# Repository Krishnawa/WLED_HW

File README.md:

# WLED_HW
a WLED based ESP12F Hardware
You can find more information about WLED here: https://github.com/Aircoookie/WLED

## Hardware photo

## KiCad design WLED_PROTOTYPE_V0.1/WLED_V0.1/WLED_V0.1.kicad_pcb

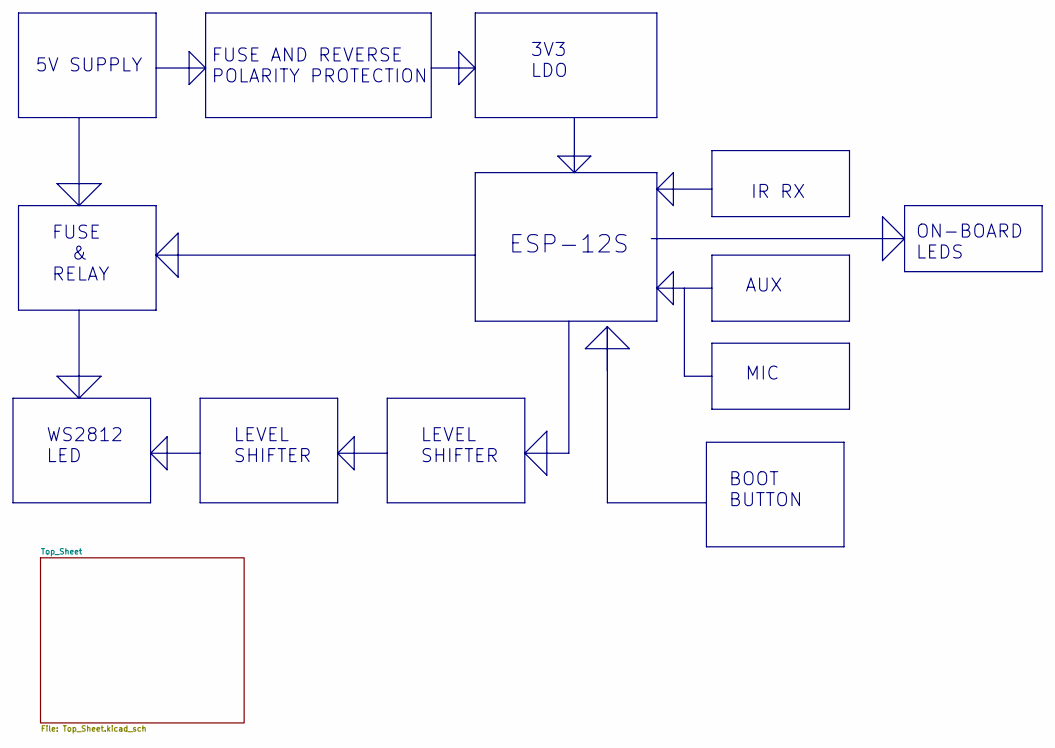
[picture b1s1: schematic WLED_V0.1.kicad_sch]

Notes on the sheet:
FUSE AND REVERSE POLARITY PROTECTION
BOOT BUTTON
WS2812 LED
LEVEL SHIFTER
ESP-12S
3V3 LDO
IR RX
FUSE & RELAY
AUX
MIC
5V SUPPLY
ON-BOARD LEDS

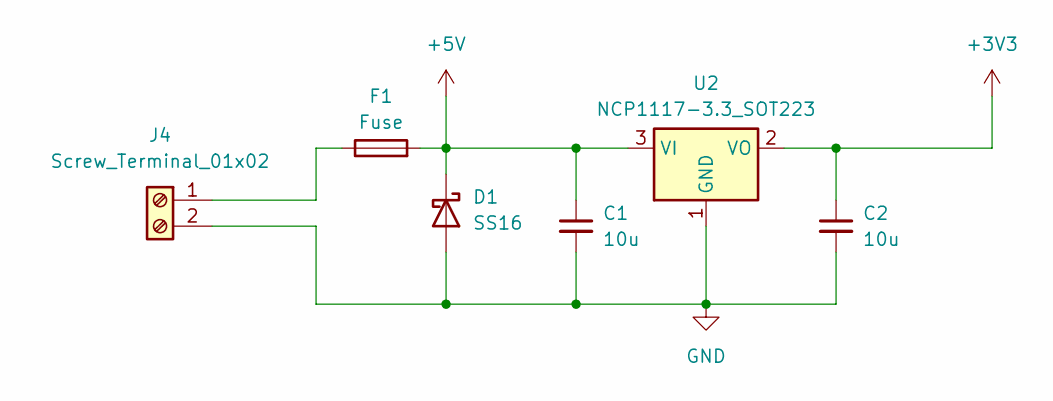
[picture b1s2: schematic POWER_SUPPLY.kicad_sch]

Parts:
C1, C2: 10u; C_0805_2012Metric
D1: SS16; D_SMA
F1: Fuse; Fuse_0805_2012Metric
J4: Screw_Terminal_01x02; TerminalBlock_Phoenix_MKDS-1,5-2_1x02_P5.00mm_Horizontal
U2: NCP1117-3.3_SOT223; SOT-223-3_TabPin2

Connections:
+5V: C1.1, D1.1 (K), F1.2, U2.3 (VI); also elsewhere on the board
GND: C1.2, C2.2, D1.2 (A), J4.2, U2.1 (GND); also elsewhere on the board
unnamed: F1.1, J4.1

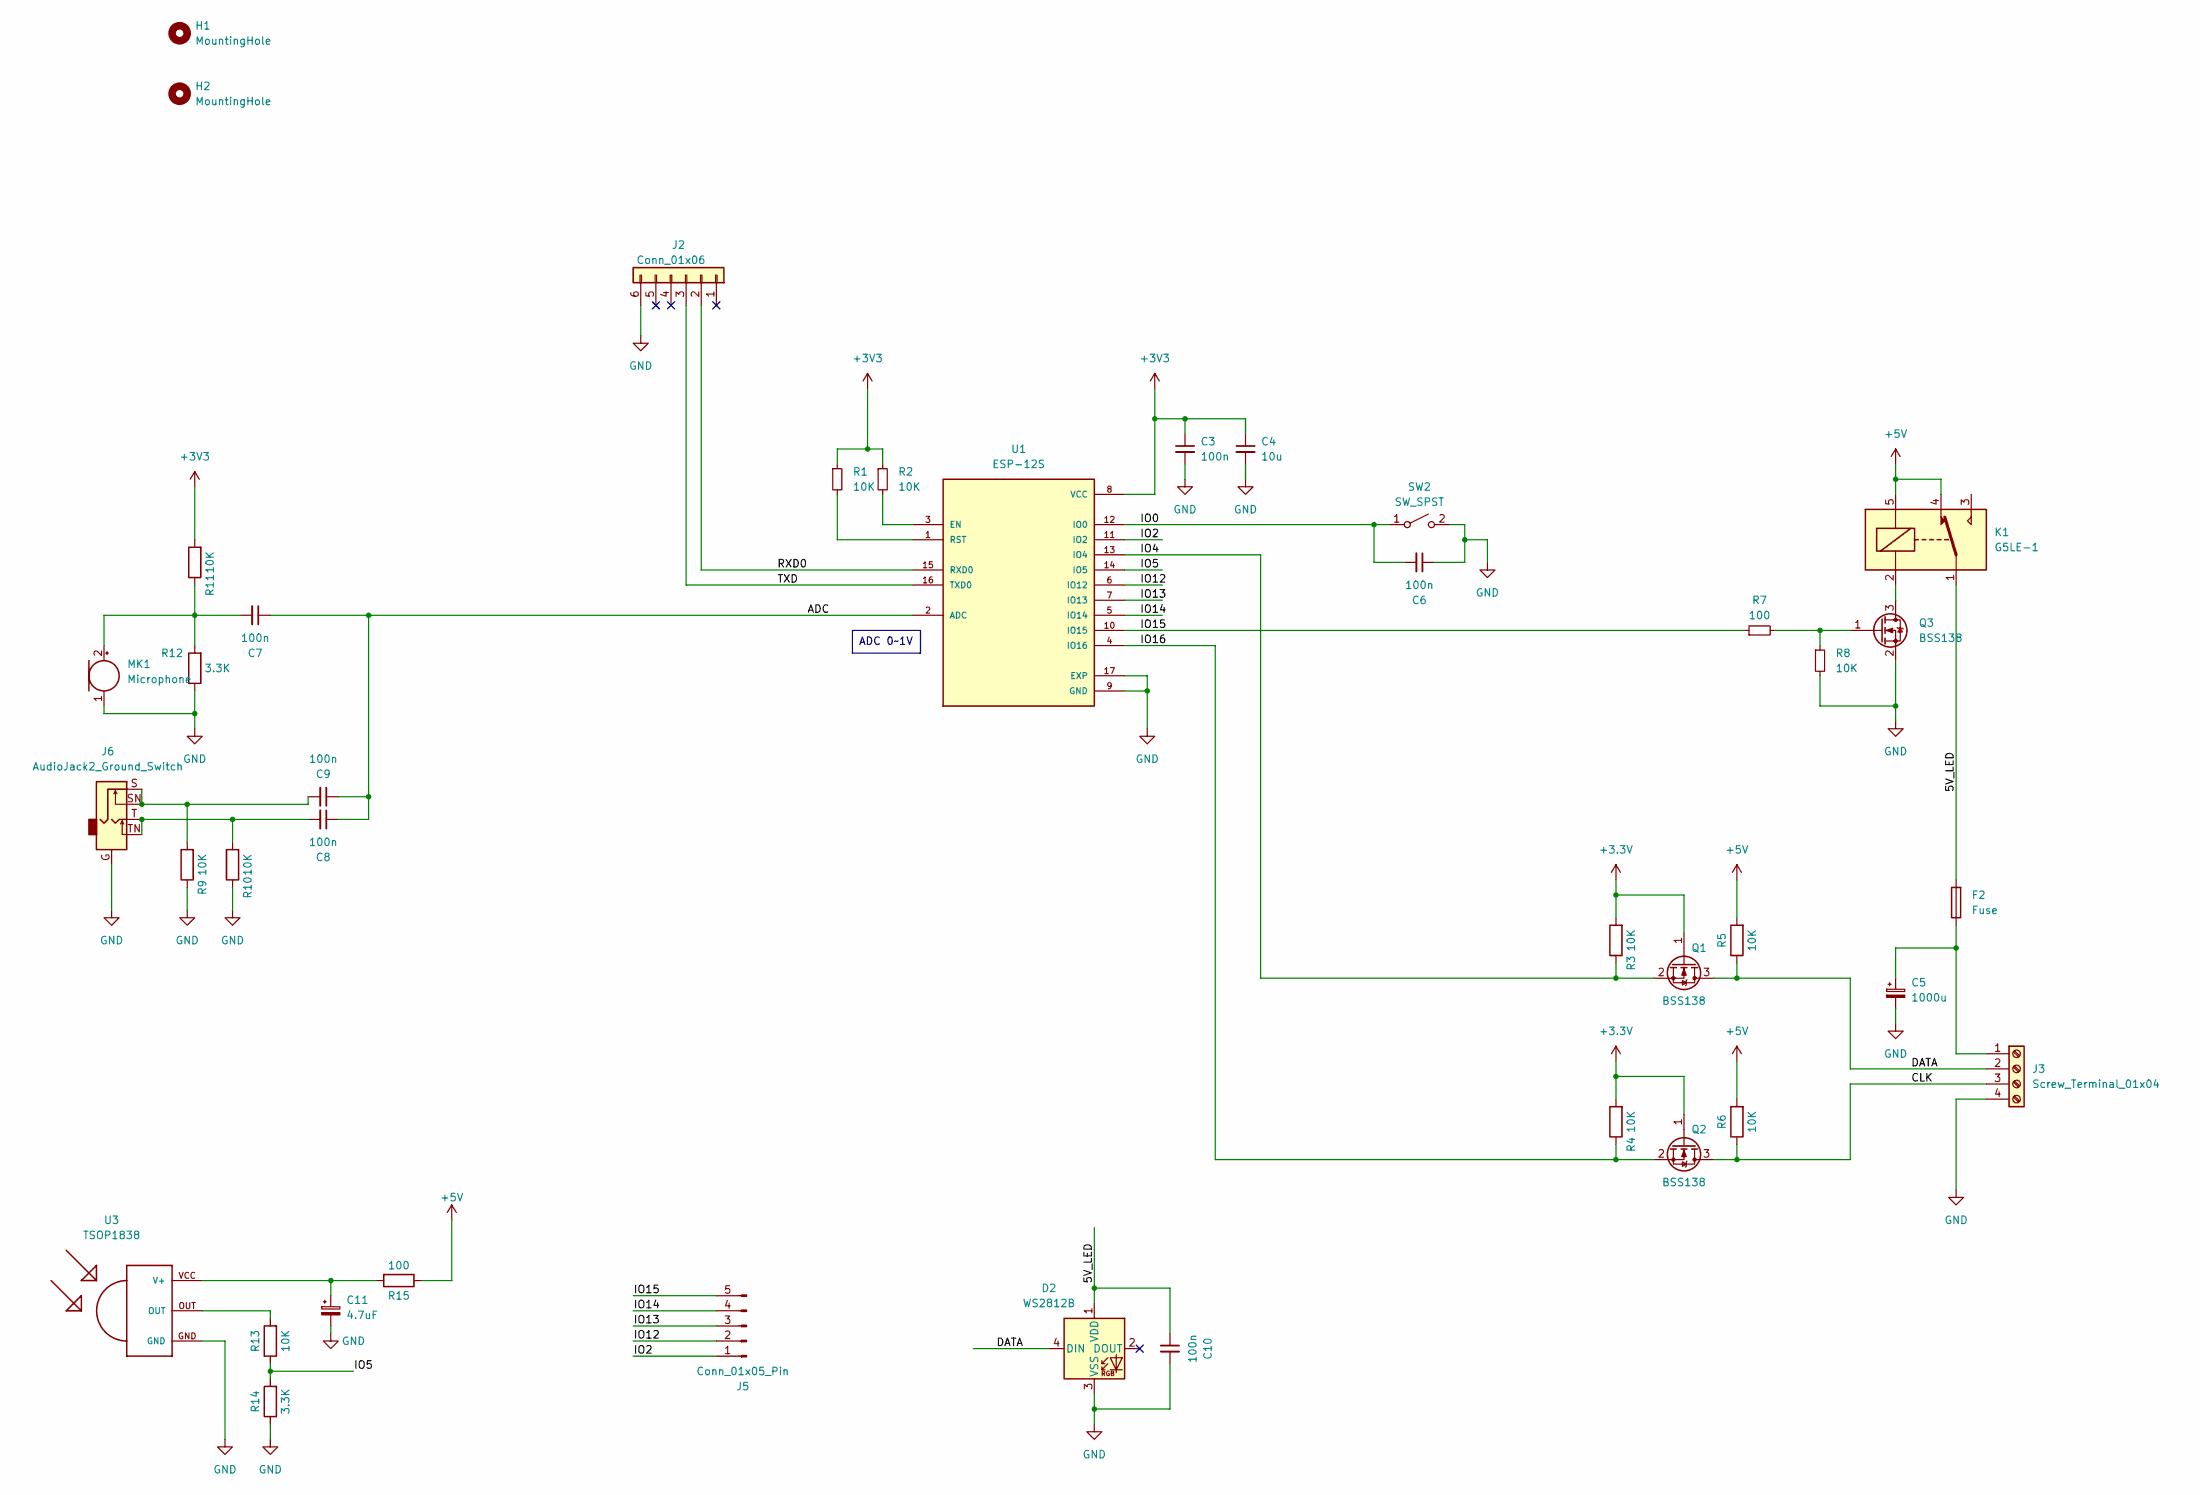
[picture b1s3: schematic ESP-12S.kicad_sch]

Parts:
C3, C6, C7, C8, C9, C10: 100n; C_0805_2012Metric
C4: 10u; C_0805_2012Metric
C5: 1000u; CP_Radial_D10.0mm_P5.00mm
C11: 4.7uF; C_0805_2012Metric
D2: WS2812B; LED_WS2812B_PLCC4_5.0x5.0mm_P3.2mm
F2: Fuse; Fuseholder_Clip-5x20mm_Keystone_3512P_Inline_P23.62x7.27mm_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
H1, H2: MountingHole; MountingHole_3mm
J2: Conn_01x06; PinHeader_1x06_P2.54mm_Vertical
J3: Screw_Terminal_01x04; TerminalBlock_Phoenix_MKDS-1,5-4_1x04_P5.00mm_Horizontal
J5: Conn_01x05_Pin; PinHeader_1x05_P2.54mm_Vertical
J6: AudioJack2_Ground_Switch; Jack_3.5mm_CUI_SJ1-3525N_Horizontal
K1: G5LE-1; Relay_SPDT_Omron-G5LE-1
MK1: Microphone; PinHeader_1x02_P2.54mm_Vertical
Q1, Q2, Q3: BSS138; SOT-23
R1, R2, R3, R4, R5, R6, R8, R9, R10, R11, R13: 10K; R_0805_2012Metric
R7, R15: 100; R_0805_2012Metric
R12, R14: 3.3K; R_0805_2012Metric
SW2: SW_SPST; SW_PUSH_6mm_H7.3mm
U1: ESP-12S; MODULE_ESP-12S; PARTREV V1.1
U3: TSOP1838; TSOP18XX

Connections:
+5V: K1.4, K1.5, R5.2, R6.2, R15.1; also elsewhere on the board
/Top_Sheet/ESP-12S/5V_LED: C10.1, D2.1 (VDD), F2.2, K1.1
/Top_Sheet/ESP-12S/ADC: C7.1, C8.1, C9.1, U1.2 (ADC)
/Top_Sheet/ESP-12S/CLK: J3.3, Q2.3 (D), R6.1
/Top_Sheet/ESP-12S/DATA: D2.4 (DIN), J3.2, Q1.3 (D), R5.1
/Top_Sheet/ESP-12S/IO0: C6.2, SW2.1 (A), U1.12 (IO0)
/Top_Sheet/ESP-12S/IO2: J5.1, U1.11 (IO2)
/Top_Sheet/ESP-12S/IO4: Q1.2 (S), R3.1, U1.13 (IO4)
/Top_Sheet/ESP-12S/IO5: R13.1, R14.2, U1.14 (IO5)
/Top_Sheet/ESP-12S/IO12: J5.2, U1.6 (IO12)
/Top_Sheet/ESP-12S/IO13: J5.3, U1.7 (IO13)
/Top_Sheet/ESP-12S/IO14: J5.4, U1.5 (IO14)
/Top_Sheet/ESP-12S/IO15: J5.5, R7.1, U1.10 (IO15)
/Top_Sheet/ESP-12S/IO16: Q2.2 (S), R4.1, U1.4 (IO16)
/Top_Sheet/ESP-12S/RXD0: J2.2, U1.15 (RXD0)
/Top_Sheet/ESP-12S/TXD: J2.3, U1.16 (TXD0)
GND: C3.2, C4.2, C5.2, C6.1, C10.2, C11.2, D2.3 (VSS), J2.6, J3.4, J6.G, MK1.1 (-), Q3.2 (S), R8.2, R9.1, R10.1, R12.1, R14.1, SW2.2 (B), U1.9 (GND), U1.17 (EXP), U3.GND; also elsewhere on the board
unnamed: C8.2, J6.T, J6.TN, R10.2
unnamed: C9.2, J6.S, J6.SN, R9.2
unnamed: C5.1, F2.1, J3.1
unnamed: C7.2, MK1.2 (+), R11.1, R12.2
unnamed: K1.2, Q3.3 (D)
unnamed: Q3.1 (G), R7.2, R8.1
unnamed: R13.2, U3.OUT
unnamed: R2.2, U1.3 (EN)
unnamed: R1.2, U1.1 (RST)
unnamed: C11.1, R15.2, U3.VCC (V+)

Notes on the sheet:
ADC 0~1V

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
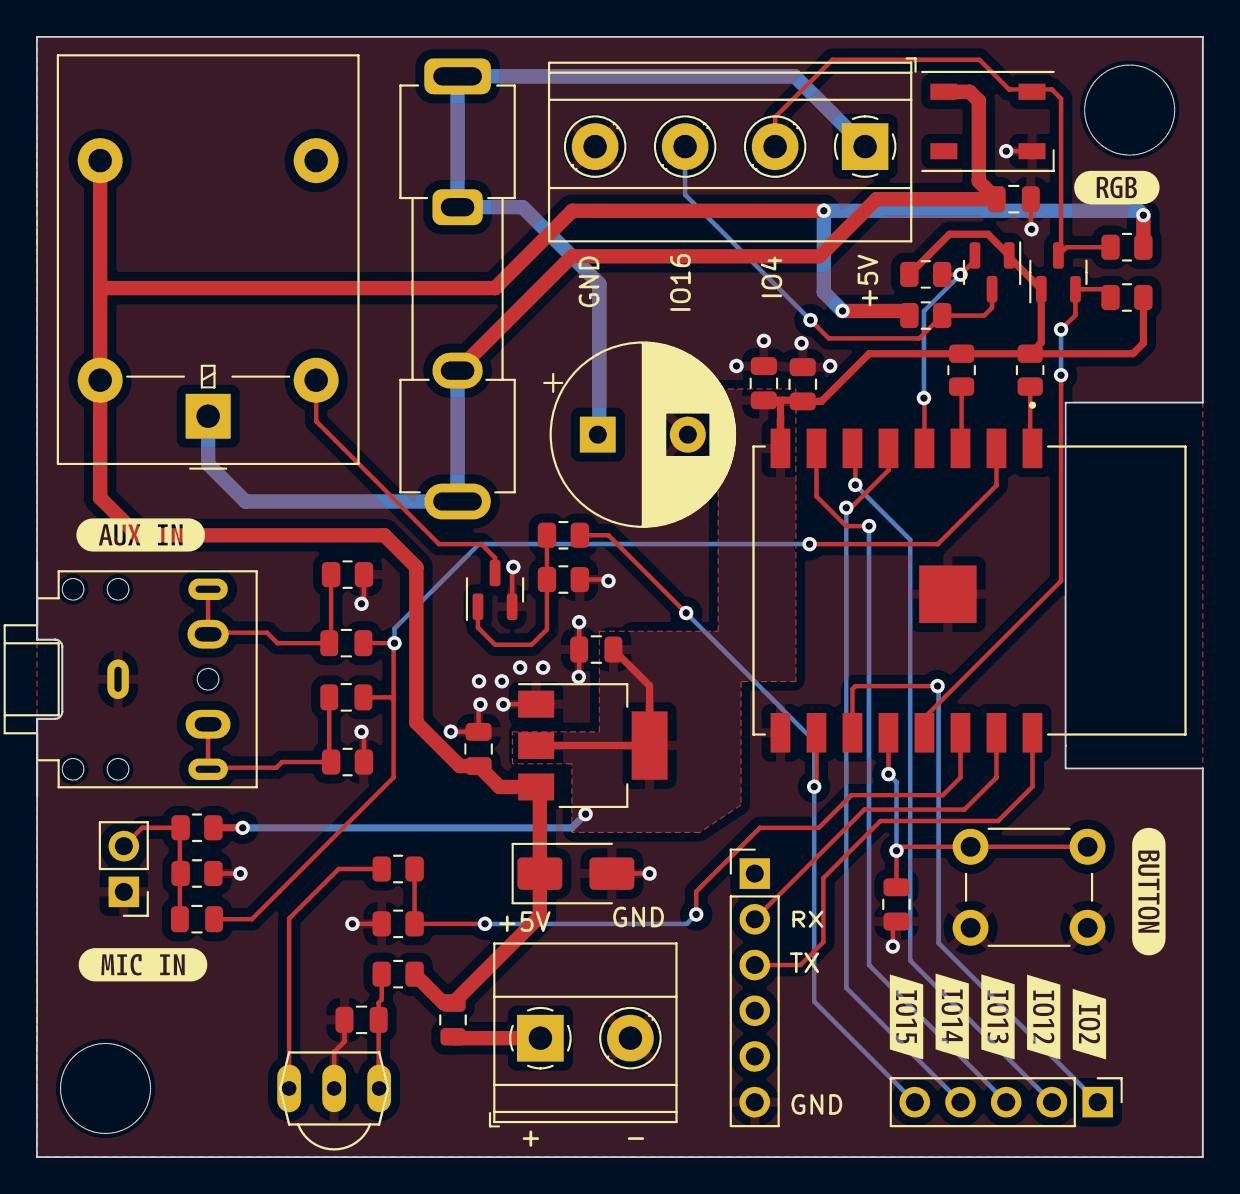
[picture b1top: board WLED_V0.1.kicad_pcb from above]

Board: 2 copper layers, 64.8 x 62.2 mm, 55 parts (0 on the bottom side), 29 nets.

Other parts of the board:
kibuzzard-6541D5B9: G***; kibuzzard-6541D5B9
kibuzzard-6541D5D1: G***; kibuzzard-6541D5D1
kibuzzard-6541D5EF: G***; kibuzzard-6541D5EF
kibuzzard-6541D591: G***; kibuzzard-6541D591
kibuzzard-6541D612: G***; kibuzzard-6541D612
kibuzzard-6541E98B: G***; kibuzzard-6541E98B
kibuzzard-6541E326: G***; kibuzzard-6541E326
kibuzzard-6541E704: G***; kibuzzard-6541E704
kibuzzard-6541E997: G***; kibuzzard-6541E997

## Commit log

2024-01-28 Added Board photo
2024-01-28 Added photos in the README
